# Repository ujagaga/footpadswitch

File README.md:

# footpadswitch
Foot pad configurable shortcut key

The intention is to build a radio frequency foot switch to activate a usb device 
which acts as a HID keyboard sending an alt/F12 key code. This can be caught by an 
application which can be configured for various tasks.
I used an RF transmit module for the foot pad controller and RF receive module for
activating a microcontroller to send the key code.
The microcontroller is AtTiny2313 and the firmware is baces on AVR USB library.

The RF receiver gets a lot of noise, so I filtered it out with an RC low pass filter.
Because of this, the controlling signal must last at least 10ms.   

I wrote the application in python, built it into a standalone windows application using py2exe
and created an installer using CreateInstall. You should start the app as an administrator to 
allow writing the config file or install somewhere you have write priviledges like user 
application folder. Once you start the app, it saves current mouse position after you press 
ctrl/F12 and uses it as location to simulate a click when it receives alt/F12. This basically 
gives you the option to generate a mouse click on a configured place on the screen. I use it 
for an application which has no keyboard shortcuts and my hands are busy, so I can not click myself.

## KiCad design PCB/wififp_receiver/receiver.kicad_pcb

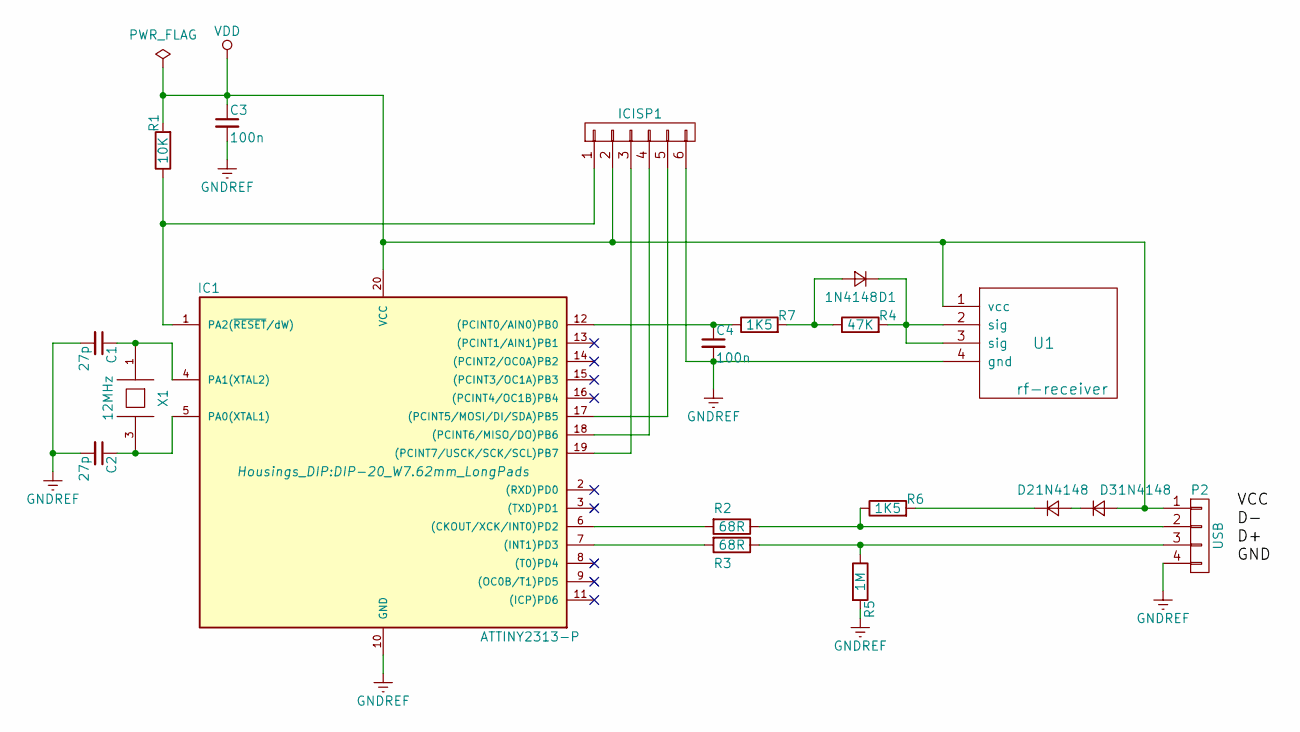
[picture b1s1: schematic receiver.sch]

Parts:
C1, C2: 27p; C_0805_HandSoldering
C3, C4: 100n; C_0805_HandSoldering
D1, D2, D3: 1N4148; D_0805
IC1: ATTINY2313-P; DIP-20_W7.62mm_LongPads
P1: ICISP1; Socket_Strip_Straight_1x06_Pitch2.54mm
P2: USB; Socket_Strip_Straight_1x04_Pitch2.54mm
R1: 10K; C_0805_HandSoldering
R2, R3: 68R; C_0805_HandSoldering
R4: 47K; C_0805_HandSoldering
R5: 1M; C_0805_HandSoldering
R6, R7: 1K5; C_0805_HandSoldering
U1: rf-receiver; Socket_Strip_Angled_1x04_Pitch2.54mm
X1: 12MHz; Crystal_HC49-U_Vertical

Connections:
GNDREF: C1.2, C2.2, C3.2, C4.2, IC1.10 (GND), P1.6, P2.4, R5.2, U1.4 (gnd)
unnamed: C1.1, IC1.4 (PA1(XTAL2)), X1.1
unnamed: C2.1, IC1.5 (PA0(XTAL1)), X1.3
unnamed: C4.1, IC1.12 ((PCINT0/AIN0)PB0), R7.1
unnamed: D1.1 (K), R4.2, U1.2 (sig), U1.3 (sig)
unnamed: D1.2 (A), R4.1, R7.2
unnamed: D2.1 (K), R6.2
unnamed: D2.2 (A), D3.1 (K)
unnamed: IC1.1 (PA2(~RESET~/dW)), P1.1, R1.1
unnamed: IC1.6 ((CKOUT/XCK/INT0)PD2), R2.2
unnamed: IC1.7 ((INT1)PD3), R3.2
unnamed: IC1.17 ((PCINT5/MOSI/DI/SDA)PB5), P1.5
unnamed: IC1.18 ((PCINT6/MISO/DO)PB6), P1.4
unnamed: IC1.19 ((PCINT7/USCK/SCK/SCL)PB7), P1.3
unnamed: P2.2, R2.1, R6.1
unnamed: P2.3, R3.1, R5.1
VDD: C3.1, D3.2 (A), IC1.20 (VCC), P1.2, P2.1, R1.2, U1.1 (vcc)

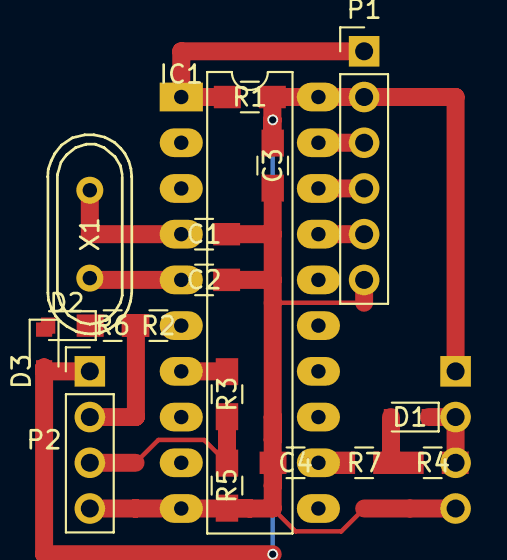
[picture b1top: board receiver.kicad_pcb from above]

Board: 2 copper layers, 19 parts (1 on the bottom side), 17 nets.

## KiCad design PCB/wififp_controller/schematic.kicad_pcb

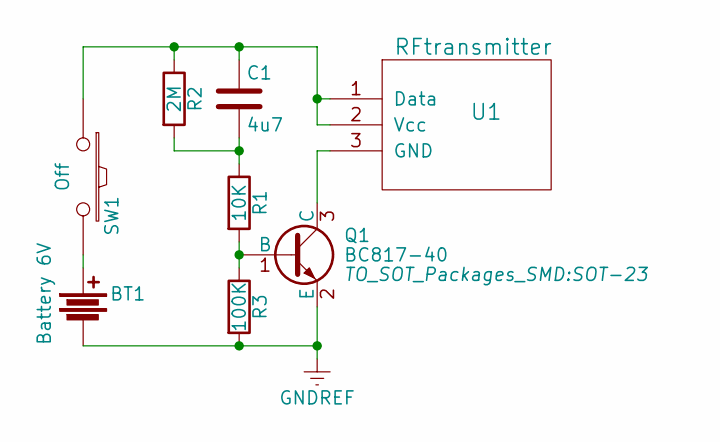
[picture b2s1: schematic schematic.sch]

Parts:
BT1: Battery 6V; 6V_battery_4LR44
C1: 4u7; C_0805_HandSoldering
Q1: BC817-40; SOT-23
R1: 10K; R_0805_HandSoldering
R2: 2M; R_0805_HandSoldering
R3: 100K; R_0805_HandSoldering
SW1: Off; Socket_Strip_Straight_1x02_Pitch2.54mm
U1: RFtransmitter; Socket_Strip_Angled_1x03_Pitch2.54mm

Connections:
GNDREF: BT1.2, Q1.2 (E), R3.2
unnamed: BT1.1, SW1.2
unnamed: C1.1, R2.1, SW1.1, U1.1 (Data), U1.2 (Vcc)
unnamed: C1.2, R1.1, R2.2
unnamed: Q1.1 (B), R1.2, R3.1
unnamed: Q1.3 (C), U1.3 (GND)

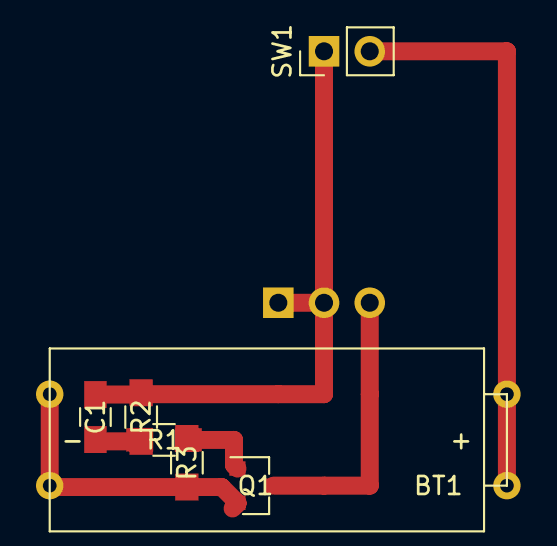
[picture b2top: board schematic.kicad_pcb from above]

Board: 2 copper layers, 8 parts (1 on the bottom side), 6 nets.

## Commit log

2017-06-29 All finished and working
2017-06-29 Updated the schematic
